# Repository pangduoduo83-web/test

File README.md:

# AI未来实践中心 - 项目驱动教学实验平台(IOEDU-New)

前后端一体的实验室设备借阅与项目驱动教学平台,复刻参考站学生端功能并新增管理员端。

## 技术栈

| 端 | 技术 |
|---|---|
| 后端 | Spring Boot 2.6.13 + Java 8 + MySQL 8 + Spring Data JPA + JWT |
| 前端 | Vue 3 + Vite 5 + Element Plus + Pinia + Vue Router 4 + ECharts |
| 小程序端 | uni-app (Vue 3 + Vite) 微信小程序,学生/教师/管理员三端,复用同一套后端接口 |

## 功能

- **学生端** `/app`:个人中心(实践统计/学习趋势/成就)、项目中心(浏览/报名/收藏/进度,详情支持富文本图文视频描述)、成果提交(整体或分阶段考核项提交/截图上传/查看评分评语/加权综合分)、设备图书馆(筛选/详情/三步借阅申请/心愿单跨端同步)、借阅管理(撤销/归还/到期前3天可续借一次)、技能评估(雷达图/测评/学习建议)、站内通知(含到期归还提醒)
- **教师端** `/teacher`:教学工作台(名下项目统计)、教学资源管理(真实附件上传,学生端可直接下载)、更换项目封面、学生报名进度查看
- **管理员端** `/admin`:数据看板(趋势图/设备利用率)、设备管理 CRUD(富文本描述/文档附件上传/CSV相关)、借阅审批(批准/拒绝/归还验收,联动库存)、项目管理 CRUD(指派讲师/富文本描述图片视频/成果考核项权重设置/BOM CSV导入)、报名进度管理、成果评审(支持分阶段考核项与AI预评审)、通知管理(群发/删除)、讨论管理(删帖级联回复)、用户管理(新建/CSV批量导入/重置密码/禁用/删除/三级角色)、站点设置(标题/LOGO/底部信息/注册开关/分页/分类)、AI 设置
- **落地页** `/` 与登录注册 `/auth`

## AI 功能(网页端与小程序端同步支持)

- **AI 学习规划师**(技能评估页):基于六维技能画像与项目库,后端先确定性计算项目匹配分,大模型在候选内生成学习画像总结、重点提升维度与「基础补强 → 综合实践 → 挑战提升」三阶段项目路线;AI 不可用时自动降级为智能匹配结果
- **AI 成果预评审**(管理端评分弹窗):AI 阅读学生成果说明,给出建议分、亮点/不足与评语草稿,自动填入评分表单,最终由教师确认修改
- **稳定性**:服务端代理调用(密钥不出后端)、结果结构校验与项目 ID 白名单、每用户限流(3次/小时)、10 分钟缓存、超时+熔断+规则降级

### AI 助手与 SKILL(`/app/ai`)

- **SKILL**:一段可复用的 AI 能力 = 系统提示词 + 输入结构(JSON Schema,可选表单)+ 工具白名单 + 模型参数,定义为一份 spec JSON。内置 SKILL 在 `src/main/resources/skills/*.json`(学习助手、设备借用顾问、项目推荐官、BOM 审查员),用户可「另存为」后自定义;教师/管理员可创建本站共享 SKILL,管理员可把个人 SKILL 提升为本站共享。
- **工具(Tool)**:模型可调用的平台能力,定义形状 `{name, description, inputSchema}` 与 MCP Tool / OpenAI function 一致(`ai/tool/AiTool.java`,实现类注册为 bean 即自动进入 `ToolRegistry`)。内置只读工具:`equipment.search/get`、`project.search/get`、`borrow.my_list`、`skill.my_scores`;写操作 `borrow.apply` 执行前必须经用户确认。管理员在「AI 中心 → 工具策略」可关闭工具、限制角色、强制确认、设每日次数。
- **对话**:`POST /api/ai/chat/stream` 为 SSE 流式(事件 delta / tool_call / tool_result / confirm_required / done / error),`POST /api/ai/chat` 为非流式;会话历史、运行审计(`ai_runs` / `ai_tool_invocations`)与每日用量(`IOEDU_AI_DAILY_RUNS`,默认 50 次/人/天)均入库。
- **为 Agent 预留**:`LlmGateway` 抽象了 OpenAI 兼容协议(含 tools 与 stream),日后升级 Boot 3 可换 Spring AI 实现;SKILL 的 inputSchema 即工具参数定义,可直接被 Agent 当工具编排;工具定义按 MCP 形状设计,加一个 MCP Server 端点即可对外暴露。
- 本地联调:`node scripts/mock-ai-server.mjs` 已支持流式与工具调用,后端设 `IOEDU_AI_BASE_URL=http://localhost:9281 IOEDU_AI_API_KEY=mock-key`。

### 配置(不配则 AI 自动降级,平台其余功能不受影响)

**推荐方式:管理后台在线配置(免重启)** —— 管理员登录 → 「AI 设置」页,填接口地址/模型/API Key,可调输出 Token 上限、温度、超时,支持 DeepSeek/通义千问一键预设与**连接测试**,保存后立即生效。配置存数据库,优先级高于环境变量。

环境变量方式(作为默认值,适合初始部署):

```bash
# 本地开发:设置环境变量后启动后端
IOEDU_AI_API_KEY=sk-xxx                        # DeepSeek 或通义千问的 API Key
IOEDU_AI_BASE_URL=https://api.deepseek.com     # 选填,默认 DeepSeek
IOEDU_AI_MODEL=deepseek-chat                   # 选填,默认 deepseek-chat

# Docker 部署:项目根目录 .env 文件写 AI_API_KEY=sk-xxx(可选 AI_BASE_URL / AI_MODEL)
```

通义千问填法:`https://dashscope.aliyuncs.com/compatible-mode` + `qwen-plus`。
本地联调可不买 Key:先 `node scripts/mock-ai-server.mjs` 起模拟模型,再在 AI 设置页填 `http://localhost:9281` + 任意 Key。

## 多租户(一套后端服务多个客户)

后端为单进程多租户:每个客户一个独立 MySQL 库 `ioedu_<编码>`,按请求 Host 的子域名(`c001.根域`)切库,数据、登录令牌、上传文件三层隔离;老部署的 `ioedu` 库自动成为默认租户。开通客户通过平台接口 `POST /api/platform/tenants`(静态令牌 `IOEDU_PLATFORM_TOKEN` 鉴权),本地联调可用 `X-Tenant-Id` 请求头切换租户,`smoke-test-tenant.ps1` 覆盖开通、隔离、停用、注销全流程。详见《部署指南.md》5.2 节。

## 项目商店(跨客户共享项目)

`hub/` 是独立的商店服务(Spring Boot 2.6 / Java 8,库 `ioedu_hub`,端口 8081)。客户站点管理员在「管理后台 → 项目商店」、教师在「教师工作台」把本地项目发布到商店,或在商店里安装项目(附件随之搬运、本地记住上游版本以便更新);平台管理员在 `/platform/login` 登录平台控制台:审核上架、设置可见范围与定向分享,以及在「客户站点」页一键开通新客户(建库 + 初始化管理员 + 商店登记 + 写入接入密钥)。本地开发:`cd hub && mvn spring-boot:run -Dspring-boot.run.profiles=dev`(平台管理员 `platform / platform123`),主后端 dev profile 已默认指向 `http://localhost:8081`。详见《部署指南.md》5.3 节。

## 快速启动

### 1. 数据库

本地安装 MySQL 8,确认 root 密码。默认配置连接 `localhost:3306`,首次启动自动建库 `ioedu`,由 Flyway 执行 `src/main/resources/db/migration/` 下的脚本建表(Hibernate 只做校验,不再自动改表;以后改表结构请新增 `V{n}__xxx.sql`)。

数据库密码默认 `123456789`,可用环境变量 `IOEDU_DB_PASSWORD` 覆盖(也可覆盖 `IOEDU_DB_URL` / `IOEDU_DB_USERNAME`)。

### 2. 后端(端口 8080)

本地开发请激活 **dev profile**:它提供内置开发 JWT 密钥、写入演示数据(10 个项目 + 12 台设备 + 演示账号)并把管理员设为 `admin@ioedu.cn / admin123`,`smoke-test.ps1` 依赖这些数据。

```bash
start-backend.bat
# 等价于 mvn spring-boot:run -Dspring-boot.run.profiles=dev
# IDEA 里运行 IoeduNewApplication 时在 Run Configuration 加 --spring.profiles.active=dev
```

不带 profile 启动就是生产模式:必须设置 `IOEDU_JWT_SECRET`(≥32 字符),不写演示数据,首个管理员密码来自 `IOEDU_ADMIN_PASSWORD`(留空则随机生成并打印到日志)。

### 3. 前端(端口 5173)

```bash
cd frontend
npm install
npm run dev
```

浏览器访问 http://localhost:5173 ,开发代理已把 `/api` 转发到 8080。

### 4. 微信小程序端(可选)

```bash
cd miniprogram
npm install
npm run dev:mp-weixin
```

微信开发者工具导入 `miniprogram/dist/dev/mp-weixin`,本地设置勾选「不校验合法域名」即可联调,详见 `miniprogram/README.md`。

## Docker 一键部署(生产)

服务器装好 Docker 后,在项目根目录执行:

```bash
docker compose up -d --build
```

将启动 3 个容器:`ioedu-mysql`(数据卷持久化)、`ioedu-backend`(8080,仅内网)、`ioedu-frontend`(Nginx,对外 8093 端口,反代 /api)。浏览器访问 http://服务器IP:8093 即可。

- 首次部署先 `cp .env.example .env` 并填写:`JWT_SECRET`(必填,≥32 随机字符)、`DB_PASSWORD`、`ADMIN_PASSWORD`(可留空随机生成并打印到日志)等,详见《部署指南.md》
- 更新发版:`git pull && docker compose up -d --build`
- 查看日志:`docker compose logs -f backend`
- 国内服务器 npm 下载慢:取消 `frontend/Dockerfile` 中 npmmirror 注释

## 演示账号(仅 dev profile / `IOEDU_SEED_DEMO=true` 时存在)

| 角色 | 邮箱 | 密码 |
|---|---|---|
| 管理员 | admin@ioedu.cn | admin123(dev profile 默认;生产由 `IOEDU_ADMIN_PASSWORD` 指定或随机生成) |
| 学生 | zhang@stu.ioedu.cn | 123456 |
| 教师(陈老师) | chen@ioedu.cn | 123456 |
| 教师(李老师/王老师/赵老师) | li@ioedu.cn / wang@ioedu.cn / zhao@ioedu.cn | 123456 |

## 目录结构

```
IOEDU-New/
├── pom.xml
├── src/main/java/com/example/ioedunew/
│   ├── common/       # 统一响应、异常处理
│   ├── config/       # JWT、认证拦截器、CORS
│   ├── controller/   # 学生端 + 管理端 REST 接口
│   ├── dto/          # 请求/响应模型
│   ├── entity/       # JPA 实体(8 张表)
│   ├── repository/   # 数据仓库
│   ├── service/      # 业务服务(借阅状态机、库存控制等)
│   └── init/         # 启动种子数据
├── src/main/resources/
│   ├── application.properties
│   └── seed/         # 项目与设备种子 JSON
├── frontend/         # Vue 3 前端(学生端 + 管理端)
├── miniprogram/      # uni-app 微信小程序端(学生/教师/管理员)
└── IoeduFront/       # 旧 Vue2 脚手架(已废弃,可删除)
```

## 借阅状态机

```
PENDING(审批中) ─ 批准 → APPROVED(借用中,扣库存) ─ 学生申请归还 → RETURN_REQUESTED ─ 管理员验收 → RETURNED(回补库存)
      │                                     
      ├─ 拒绝 → REJECTED
      └─ 学生撤销 → CANCELLED
```

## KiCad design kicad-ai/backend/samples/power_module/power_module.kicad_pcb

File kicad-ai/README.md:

# KiCad AI Assistant · Web（多用户版）

基于 **LangGraph + Deep Agents** 重新实现的 KiCad 智能助手，参考开源项目
[paul356/KiCad-AI-Assistant](https://github.com/paul356/KiCad-AI-Assistant)（一个内嵌在 KiCad 里的 wxPython 插件），
把它改造成 **多用户在线使用的 Web 应用**：

- 每个用户拥有独立账号、独立工作区（上传的 KiCad 工程）、独立对话历史与独立长期记忆；
- Agent 通过工具读写 `.kicad_pcb` / `.kicad_sch` 文件：查询元件、移动/对齐/分布封装、运行 DRC、提取网表、保存/恢复快照；
- 页面按设计稿实现：左侧导航 + 对话历史，中间流式对话（工具调用卡片、DRC 结果卡片、任务清单、人工确认卡片），右侧当前工程 / 布局预览 / 可用工具 / 会话状态 / 在线用户；
- 产品首页（`/`）+ 登录页（`/login`）+ 工作台（`/app`）+ **后台管理**（`/admin`：模型配置热重载、用户管理、系统设置、用量总览）。

## 架构

```
┌────────────── frontend (React + Vite + Tailwind) ──────────────┐
│  登录/注册 · 对话历史 · SSE 流式消息 · 工具卡片 · 布局预览 · 在线用户 (WebSocket) │
└──────────────────────────────┬──────────────────────────────────┘
                               │ REST + SSE + WS (JWT)
┌──────────────────────────────▼──────────────────────────────────┐
│ backend (FastAPI)                                                │
│  api/      auth · projects · conversations · chat(stream/resume) · tools · presence │
│  agent/    create_deep_agent(...) ← 单个进程级图，按 thread_id / context 隔离用户   │
│            ├─ tools/native       53 个内置 KiCad 工具（无需安装 KiCad）              │
│            ├─ tools/kcaa_direct  开源插件 kcaa 的 116 个工具，进程内直接调用（无 MCP）│
│            ├─ tools/mcp          可选：改为连接外部 kcaa MCP 服务器                  │
│            ├─ backends       UserWorkspaceBackend：虚拟文件系统按调用用户作用域       │
│            ├─ middleware     路径越界拦截 · 修改前自动快照 · 结果预算 · 循环守卫      │
│            ├─ executor       用户批准后由服务端按序执行整批修改计划                   │
│            ├─ budget         单次运行 token 预算（步数上限之外的成本护栏）            │
│            ├─ subagents      pcb-layout-agent / drc-agent / schematic-agent（只读）  │
│            ├─ skills/        SKILL.md（按需加载的工作流，仅管理员可编辑）             │
│            └─ memory         /memories/AGENTS.md → StoreBackend(namespace=用户)     │
│  services/runs  后台运行管理：运行与 HTTP 连接解耦，SSE 可断线重连/回放             │
│  kicad/    S 表达式解析器 · PCB/原理图模型 · 轻量 DRC · SVG 渲染 · kicad-cli 集成    │
│  db/       SQLAlchemy(users/projects/conversations)                                  │
│  LangGraph checkpointer + store：SQLite（默认）或 PostgreSQL（生产）                   │
└──────────────────────────────────────────────────────────────────┘
```

### Deep Agents 的使用方式

主代理会按本轮任务筛选原理图或 PCB 工具；同步、跨领域和不明确的任务保留完整工具。
筛选使用本地规则，不增加模型请求。执行中可通过 `expand_design_tools` 补充另一领域的工具，
扩展仅作用于当前用户轮次，仍受角色权限、整批审批和工作区边界约束。
聊天输入框与导航只订阅自身需要的状态；预览将 180 ms 内的连续变更合并请求，取消过时请求，并保留旧图直到新图就绪。

| 能力 | 实现 |
| --- | --- |
| 主代理 | `deepagents.create_deep_agent(model, tools, system_prompt, middleware, subagents, skills, memory, backend, interrupt_on, context_schema, checkpointer, store)` |
| 多用户隔离 | `thread_id = 对话 id`；`context_schema=AgentContext(user_id, role, 工程路径…)`；工具通过 `ToolRuntime.context` 拿到当前用户，只能访问自己的工作区。Deep Agents 的虚拟文件系统（`ls`/`read_file`/`write_file`…）由 `UserWorkspaceBackend` 在每次调用时解析到调用者的目录，`/data/workspaces/<id>/…`、宿主机绝对路径等任何写法都无法触及其他用户 |
| 长期记忆 | Deep Agents 自带文件记忆：`memory=["/memories/AGENTS.md"]`，`/memories/` 路由到 `StoreBackend(namespace=("memories", user_id))`；页面「设置」中可直接查看/编辑；上限 6000 字符（注入每次请求的系统提示） |
| 技能 | `skills=["/skills/"]` → `FilesystemBackend(backend/app/agent/skills)`，只读；`add_skill/append_to_skill/delete_skill` 仅管理员可见可用且需人工确认（技能对全站用户生效） |
| 子代理 | 三个声明式 `SubAgent`，各自只拿到本领域的**只读**工具；它们产出动作列表，由主代理提交计划 |
| 任务规划 | `TodoListMiddleware` → 页面显示任务清单 |
| 可视选区 | PCB/原理图预览支持单击与拖框选择对象；参考号和真实边界由服务端重新校验后注入 Agent 上下文 |
| 项目约束 | 每个工程保存线宽、间距、过孔、板边和高度约束；既注入提示词，也由中间件强制拦截违规参数 |
| 整批确认 | Agent 先调用 `submit_change_plan` 展示完整动作与参数；用户一次批准后，**由服务端按序执行全部动作**（`agent/executor.py`，每步自动快照并生成差异），模型只收到结果并运行只读验证——不再让模型逐条复述参数，消除计划与执行之间的漂移和重复审批。直接调用修改工具会被拒绝 |
| 运行与连接解耦 | 每次对话在服务端后台任务中执行（`services/runs.py`），事件带序号缓冲；刷新页面、切换对话或网络抖动都不会中断，客户端可用 `GET /api/chat/{id}/events?after=<seq>` 重连回放；只有显式「停止」会取消 |
| 成本与循环护栏 | 步数上限之外：单次运行时长上限、token 预算（`RunBudgetMiddleware`）、近似重复调用与单工具单轮调用次数守卫；工具结果超过预算时自动裁剪最大列表并把完整结果存到工作区 `.agent/tool_results/`，模型可用 `read_file`/`grep` 分页读取 |
| 上下文摘要 | 模型按预设或 `LLM_CONTEXT_TOKENS` 声明 `max_input_tokens`，Deep Agents 的摘要中间件在 85% 窗口触发（否则对自定义模型会退回 170k 的固定阈值，128k 模型永远先溢出） |
| 设计审查 | `run_design_review` 合并 KiCad 10 ERC/DRC、布局分项评分和可自动处理建议；修复后复查并对比分数 |
| ECO 同步 | `run_eco_check` 比较原理图与 PCB；`update_pcb_from_schematic` 经整批批准后补齐封装并同步值与焊盘网络，删除/替换类差异留给人工 |
| BOM/DFM | `analyze_bom` 归并物料并检查可制造性（封装库校验、超小封装、双面贴装等）；`/bom.csv` 导出 |
| 电路向导 | `preview_circuit_template` / `apply_circuit_template`：6 个基于 KiCad 标准库的参数化模板，E24 选值，经审批后用 kcaa 工具放置、设封装、连线、标注网络 |
| 框架策略 | `KiCadPolicyMiddleware.awrap_tool_call`：计划白名单、设计约束、路径越界拦截、修改前 `save_version`、成功后发 `file_changed` 与 diff |
| 流式 | `agent.astream(..., stream_mode=["updates","messages","custom"], subgraphs=True, version="v2")` → 扁平化为 SSE 事件 |

## 快速开始

### 1. 后端

```powershell
cd backend
python -m venv .venv
.\.venv\Scripts\python -m pip install -r requirements.txt
copy ..\.env.example ..\.env     # 填写 LLM_API_KEY；或设 LLM_PROVIDER=mock 离线体验
.\.venv\Scripts\python -m uvicorn app.main:app --reload --port 8000
```

API 文档：http://127.0.0.1:8000/docs

### 2. 前端

```powershell
cd frontend
npm install
npm run dev          # http://127.0.0.1:5173 （已配置 /api、/ws 代理到 8000）
```

一键脚本：`scripts\dev.ps1`（Windows）/ `scripts/dev.sh`（Linux/macOS）。

### 3. 使用

1. 注册账号（第一个用户自动成为管理员）。
2. 右侧「切换工程」→ 「加载示例：power_module」，或导入自己的 KiCad 工程 ZIP / 上传 `.kicad_pcb`、`.kicad_sch`。
3. 在对话框输入，例如：
   > 帮我优化一下电源模块的布局，电容尽量靠近芯片的电源引脚，并检查是否有 DRC 问题。
4. 观察工具调用卡片、DRC 结果卡片、右侧布局预览的实时更新；破坏性操作会弹出确认卡片。
5. 「会话快照」中可以回滚任何一次自动/手动快照。

### LLM 配置

| 提供方 | `.env` |
| --- | --- |
| OpenAI | `LLM_PROVIDER=openai` `LLM_MODEL=gpt-5.6` `LLM_API_KEY=sk-...` |
| Anthropic | `LLM_PROVIDER=anthropic` `LLM_MODEL=claude-sonnet-5` |
| DeepSeek / Qwen / Moonshot / GLM / Ollama 等 OpenAI 兼容 | `LLM_PROVIDER=custom` `LLM_BASE_URL=https://api.deepseek.com/v1` `LLM_MODEL=deepseek-v4-flash` |
| 离线演示 | `LLM_PROVIDER=mock`（脚本化模型，会真实调用两个只读工具并总结；`LLM_MOCK_DELAY_MS` 可加入每次调用的人工延迟，方便演示断线重连） |

运行护栏（均可在后台「系统设置」热更新）：`AGENT_RECURSION_LIMIT`（步数）、`AGENT_RUN_TIMEOUT_SECONDS`（单次运行时长，默认 1800）、
`AGENT_RUN_TOKEN_BUDGET`（单次运行 token 总量，默认 300 万）、`TOOL_RESULT_MAX_CHARS`（工具结果字符预算，默认 24000）。
触发任一上限时运行暂停、进度保留，页面提供「继续执行」。

思考模式由 `LLM_THINKING=default|off|fast|deep` 控制（默认 `off`，适合工具密集型 Agent）。`fast` 在支持推理档位的模型上使用最低 effort，否则使用 `LLM_THINKING_BUDGET`；`deep` 使用模型的完整推理能力。百炼、DeepSeek、GLM、Kimi、vLLM/SGLang 与 Ollama 的参数协议会根据 Base URL 自动识别，也可通过 `LLM_THINKING_STYLE` 手动指定。聊天输入框可按请求切换同一 API 端点下的模型和思考档位，模型返回的思考过程会实时折叠展示并随会话保存。

### 开源插件 KiCad-AI-Assistant 的调用方式（进程内直连，无 MCP）

上游插件的工具本质上是普通 Python 函数，MCP 只是其传输层。本项目把 PyPI 包 `kcaa` 作为依赖装入后端进程，
`backend/app/agent/tools/kcaa_direct.py` 在启动时收集其全部工具函数与参数 schema，用极简上下文替代 FastMCP `Context`
（日志 / 进度 / 缓存），直接包装为 LangChain 工具——116 个工具与 53 个内置工具合并为一个工具目录（去重后 124 个），
同名工具优先内置实现，所有路径参数仍经中间件校验在用户工作区内。

- `KCAA_MODE=direct`（默认）/ `off`；后台「系统设置」可热切换。
- 需要 `KICAD_VERSION`（默认 10.0）。符号 / 封装检索与 `add_symbol_to_schematic` 依赖 KiCad 官方库：Docker 镜像基于官方 `kicad/kicad:10.0.5`，内置匹配版本的库与预建索引；裸机部署把 `KICAD_APP_PATH` 指到 KiCad 的 share 目录即可，`sym-lib-table` / `fp-lib-table` 缺失时启动会自动生成（`backend/app/kicad/libraries.py`）。「从原理图更新 PCB」是 IPC 工具，仍需在本机 KiCad 中执行（F8）。
- 仍可选 MCP 方式：在不含 `kcaa` 的环境安装 `requirements-mcp.txt`，`KCAA_MODE=mcp` + `KCAA_MCP_URL`。

### 生产部署

- `docker compose up -d --build`：单个 `app` 容器（含开源插件库与已构建的前端），SQLite 持久化在卷 `/data`；叠加 `docker-compose.postgres.yml` 可换成 PostgreSQL。
- 运行阶段基于官方 **KiCad 10.0.5** CI 镜像（可用 `KICAD_IMAGE_TAG` 固定其他 10.0 补丁版本），包含 `kicad-cli` 与匹配的符号/封装库，并预建检索索引；KiCad 10 可以读取旧工程。工程文件窗口会显示文件格式与服务器 CLI 的兼容状态，较新格式不会再被较旧 CLI 静默处理。
- 或者 `npm run build` 后直接由 FastAPI 托管 `frontend/dist`。
- 务必修改 `JWT_SECRET`；如需关闭注册设置 `ALLOW_REGISTRATION=false`。
- 有 `kicad-cli` 时 DRC 使用 KiCad 引擎、预览可用官方 SVG 渲染；裸机未安装 KiCad 则退回内置轻量 DRC 与内置渲染。

## 测试

```powershell
cd backend
.\.venv\Scripts\python -m pytest -q
```

包含 S 表达式往返、PCB 移动/DRC、原理图网表、基于 mock 模型的完整 Agent 流式调用（计划审批 → 服务端执行 → 验证）、
多租户文件系统隔离、技能权限、后台运行/重连、运行预算与循环守卫、工具结果裁剪等测试。

## 目录

```
Ioedu/
├── backend/
│   ├── app/
│   │   ├── agent/        # factory · prompts · tools · middleware · executor · budget · backends · subagents · skills · memory · streaming
│   │   ├── api/          # auth · projects · conversations · chat(stream/resume/events) · tools · system(ws) · admin
│   │   ├── kicad/        # sexpr · pcb · sch · workspace · cli
│   │   ├── db/           # SQLAlchemy models & session
│   │   └── services/     # runs(后台运行) · presence · settings_store · conversation helpers
│   ├── samples/power_module/   # 示例工程（LDO 电源模块）
│   └── tests/
├── frontend/src/
│   ├── components/{layout,chat,right,modals,ui}
│   ├── store/            # zustand: auth · chat(SSE reducer) · projects · presence
│   └── lib/              # api client · types · formatters
├── docs/
├── scripts/
├── docker-compose.yml · Dockerfile · .env.example
```

## 与上游项目的对应关系

| 上游 (KiCad 插件) | 本项目 |
| --- | --- |
| `kicad_plugin/llm_client.py` 手写的 OpenAI/Anthropic 工具循环 + 上下文压缩 | `create_deep_agent`（内置 SummarizationMiddleware、工具循环、流式） |
| `tool_registry.py` 的 ToolPolicy（auto_snapshot / mark_dirty / reload） | `agent/tools/registry.py` + `KiCadPolicyMiddleware` |
| wxPython 聊天面板 | React Web UI，多用户、在线状态 |
| `kcaa` MCP 服务器（100+ 工具） | 作为 Python 库装入同一进程，工具函数直接调用（无 MCP）；另有无需 KiCad 的内置工具子集 |
| Skill 文件（Markdown） | Deep Agents skills（`SKILL.md`，按需加载） |
| 会话保存/恢复 | LangGraph checkpointer（SQLite/PostgreSQL）按对话线程持久化 |

## License

MIT

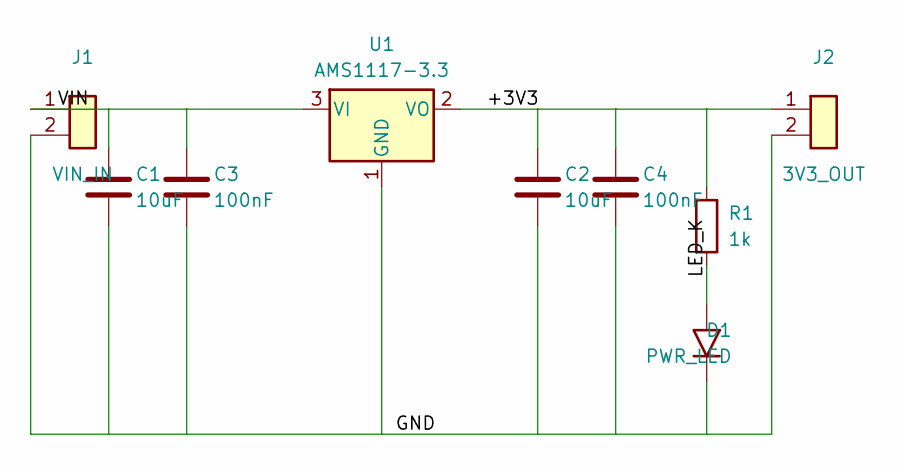
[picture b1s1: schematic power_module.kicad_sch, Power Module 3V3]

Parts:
C1, C2: 10uF; C_0805_2012Metric
C3, C4: 100nF; C_0603_1608Metric
D1: PWR_LED; LED_0603_1608Metric
J1: VIN_IN; PinHeader_1x02_P2.54mm_Vertical
J2: 3V3_OUT; PinHeader_1x02_P2.54mm_Vertical
R1: 1k; R_0603_1608Metric
U1: AMS1117-3.3; SOT-223-3_TabPin2

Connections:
+3V3: C2.1, C4.1, J2.1, R1.1, U1.2 (VO)
GND: C1.2, C2.2, C3.2, C4.2, D1.1 (K), J1.2, J2.2, U1.1 (GND)
LED_K: D1.2 (A), R1.2
VIN: C1.1, C3.1, J1.1, U1.3 (VI)

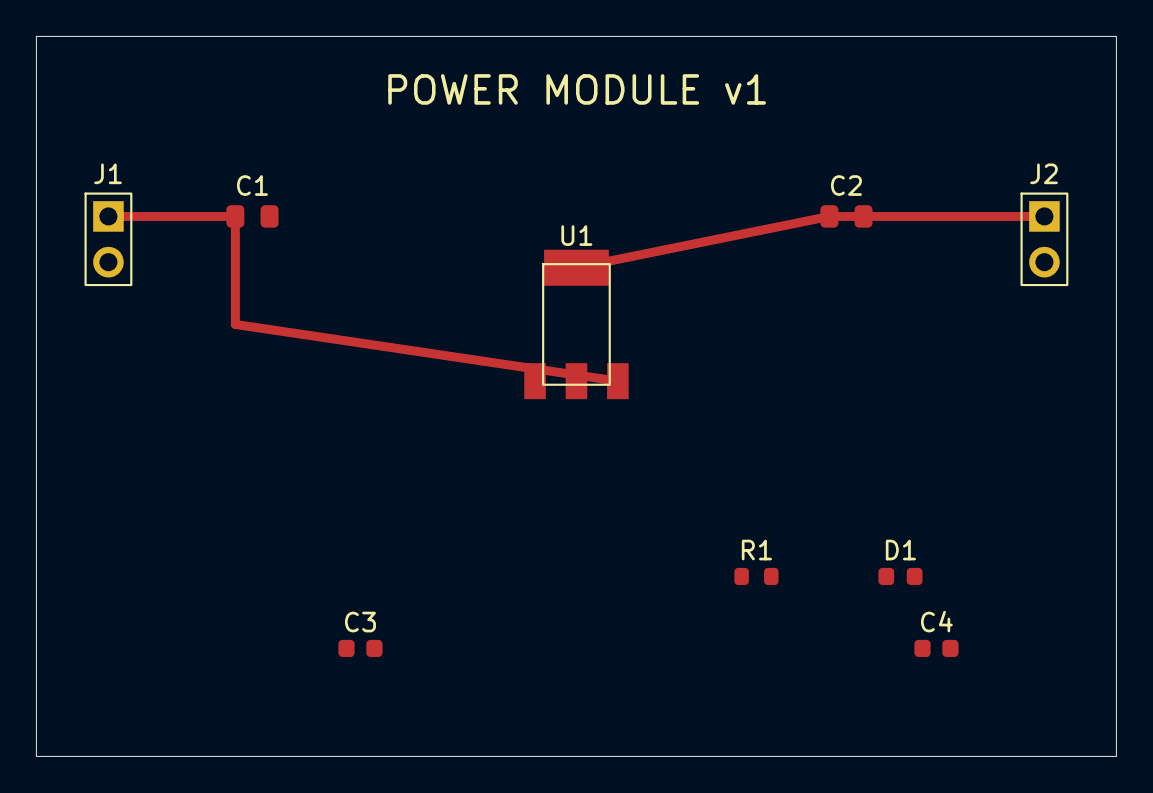
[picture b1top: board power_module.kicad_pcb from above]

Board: 2 copper layers, 60.0 x 40.0 mm, 9 parts (0 on the bottom side), 4 nets.
